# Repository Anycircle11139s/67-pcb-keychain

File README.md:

# 67-pcb-keychain
I made a custom 67 keychain that lights up when you connect it to your computer, phone or other device. I think it's really cool and I can't wait to take it to school once I build it.
<br>

<br>

<br>

<br>

<br>

BOM:
<br>

|Name              |Purpose                                |Quantity|Total Cost (USD)|Link                                                                                                                                                                                                                                                                                                                                                                                                                                                                                                                                                                                                                                                                                                                                                                               |Distributor|
|------------------|---------------------------------------|--------|----------------|-----------------------------------------------------------------------------------------------------------------------------------------------------------------------------------------------------------------------------------------------------------------------------------------------------------------------------------------------------------------------------------------------------------------------------------------------------------------------------------------------------------------------------------------------------------------------------------------------------------------------------------------------------------------------------------------------------------------------------------------------------------------------------------|-----------|
|tweezers          |to hold the small parts while soldering|1       |1.00            |https://www.aliexpress.com/item/1005008096741092.html?spm=a2g0o.productlist.main.5.7afbAQx3AQx30w&algo_pvid=4f139a33-dc3b-4da1-b521-8f96e63a979a&algo_exp_id=4f139a33-dc3b-4da1-b521-8f96e63a979a-4&pdp_ext_f=%7B%22order%22%3A%22131%22%2C%22eval%22%3A%221%22%2C%22fromPage%22%3A%22search%22%7D&pdp_npi=6%40dis%21USD%2110.81%210.99%21%21%2173.30%216.71%21%40210328df17767629735092456e2e81%2112000043710740481%21sea%21AU%217402515296%21X%211%210%21n_tag%3A-29911%3Bd%3Aef1e07f3%3Bm03_new_user%3A-29895%3BpisId%3A5000000204047332&curPageLogUid=6M5JIEKTcvOh&utparam-url=scene%3Asearch%7Cquery_from%3A%7Cx_object_id%3A1005008096741092%7C_p_origin_prod%3A                                                                                                             |ali express|
|soldering flux pen|to help me solder the smaller things   |1       |1.00            |https://www.aliexpress.com/item/1005005936689092.html?spm=a2g0o.productlist.main.7.4471xGxqxGxqcv&algo_pvid=2dcd025e-5ec3-4b9d-b2fd-4e3df81ab209&algo_exp_id=2dcd025e-5ec3-4b9d-b2fd-4e3df81ab209-6&pdp_ext_f=%7B%22order%22%3A%22353%22%2C%22spu_best_type%22%3A%22price%22%2C%22eval%22%3A%221%22%2C%22fromPage%22%3A%22search%22%7D&pdp_npi=6%40dis%21USD%216.21%210.99%21%21%2142.12%216.71%21%402101e2b017767628076321692e0a8b%2112000034926313078%21sea%21AU%217402515296%21X%211%210%21n_tag%3A-29911%3Bd%3Aef1e07f3%3Bm03_new_user%3A-29895%3BpisId%3A5000000204047332&curPageLogUid=JmLIlInXocJb&utparam-url=scene%3Asearch%7Cquery_from%3A%7Cx_object_id%3A1005005936689092%7C_p_origin_prod%3A                                                                          |ali express|
|5.1k resistor     |to resist                              |1       |0.72            |https://www.aliexpress.com/item/1005011924238866.html?spm=a2g0o.productlist.main.4.3264pH7SpH7SjC&aem_p4p_detail=202604210210197331387284447280000035590&algo_pvid=f58ab8a2-7106-4e3f-84a7-062609315ba7&algo_exp_id=f58ab8a2-7106-4e3f-84a7-062609315ba7-3&pdp_ext_f=%7B%22order%22%3A%22321%22%2C%22eval%22%3A%221%22%2C%22fromPage%22%3A%22search%22%7D&pdp_npi=6%40dis%21USD%210.53%210.53%21%21%210.53%210.53%21%40210311a017767626198982054e38ce%2112000057033019768%21sea%21AU%217402515296%21X%211%210%21n_tag%3A-29911%3Bd%3Aef1e07f3%3Bm03_new_user%3A-29895&curPageLogUid=cGjN7EKMtHuh&utparam-url=scene%3Asearch%7Cquery_from%3A%7Cx_object_id%3A1005011924238866%7C_p_origin_prod%3A&search_p4p_id=202604210210197331387284447280000035590_1                           |ali express|
|usb c receptacle  |so I can plug my computer in           |1       |1.99            |https://www.aliexpress.com/item/1005011803451264.html?productId=1005011803451264&pdp_ext_f=%7B%22eval%22:%221%22,%22fromPage%22:%22search%22,%22tabScene%22:%22retail%22,%22sku_id%22:12000056614035390,%22origProductId%22:%221005011803451264%22,%22order%22:%221%22%7D                                                                                                                                                                                                                                                                                                                                                                                                                                                                                                          |ali express|
|resetable fuse    |so no short circuit                    |1       |1.67            |https://www.aliexpress.com/item/1005008044907223.html?spm=a2g0o.productlist.main.1.4252CnoLCnoLpE&algo_pvid=10b5198a-0f95-4115-972e-984253eaf529&algo_exp_id=10b5198a-0f95-4115-972e-984253eaf529-0&pdp_ext_f=%7B%22order%22%3A%2279%22%2C%22spu_best_type%22%3A%22price%22%2C%22eval%22%3A%221%22%2C%22fromPage%22%3A%22search%22%7D&pdp_npi=6%40dis%21USD%211.67%211.67%21%21%2111.29%2111.29%21%402101d9ef17767616653342759ed8d3%2112000047100392319%21sea%21AU%217402515296%21X%211%210%21n_tag%3A-29911%3Bd%3Aef1e07f3%3Bm03_new_user%3A-29895&curPageLogUid=NiaW1SDH6kb0&utparam-url=scene%3Asearch%7Cquery_from%3A%7Cx_object_id%3A1005008044907223%7C_p_origin_prod%3A                                                                                                     |ali express|
|protection diode  |smth                                   |1       |3.37            |https://www.aliexpress.com/item/1005008923840036.html?spm=a2g0o.productlist.main.1.47e31EDi1EDimN&algo_pvid=5c20eac6-6718-47b1-babc-bcccb17ab28b&algo_exp_id=5c20eac6-6718-47b1-babc-bcccb17ab28b-0&pdp_ext_f=%7B%22order%22%3A%2227%22%2C%22eval%22%3A%221%22%2C%22fromPage%22%3A%22search%22%7D&pdp_npi=6%40dis%21USD%216.74%213.37%21%21%216.74%213.37%21%402103122117767612887433650ec1a9%2112000047220263093%21sea%21AU%217402515296%21X%211%210%21n_tag%3A-29911%3Bd%3Aef1e07f3%3Bm03_new_user%3A-29895&curPageLogUid=80s78qVBFCrP&utparam-url=scene%3Asearch%7Cquery_from%3A%7Cx_object_id%3A1005008923840036%7C_p_origin_prod%3A                                                                                                                                           |ali express|
|10uf capcitor kit |capacitate                             |1       |1.00            |https://www.aliexpress.com/item/1005010813164058.html?spm=a2g0o.productlist.main.4.7113wPJGwPJGCe&aem_p4p_detail=202604210142017673585286925940000030866&algo_pvid=14866327-1cc9-4166-a2fd-ecccc7aec23f&algo_exp_id=14866327-1cc9-4166-a2fd-ecccc7aec23f-3&pdp_ext_f=%7B%22order%22%3A%22184%22%2C%22eval%22%3A%221%22%2C%22fromPage%22%3A%22search%22%7D&pdp_npi=6%40dis%21USD%214.23%210.99%21%21%214.23%210.99%21%40210319b017767609214422619ea5ce%2112000055817174283%21sea%21AU%217402515296%21X%211%210%21n_tag%3A-29911%3Bd%3Aef1e07f3%3Bm03_new_user%3A-29895%3BpisId%3A5000000204047332&curPageLogUid=E53GmhCoiUTd&utparam-url=scene%3Asearch%7Cquery_from%3A%7Cx_object_id%3A1005010813164058%7C_p_origin_prod%3A&search_p4p_id=202604210142017673585286925940000030866_1|ali express|
|470r resistor     |to resist                              |1       |1.68            |https://www.aliexpress.com/item/1005006996501198.html?spm=a2g0o.productlist.main.1.1371Xnz8Xnz8kp&algo_pvid=fcb6f408-4475-4521-a71e-0347dbee9bc1&algo_exp_id=fcb6f408-4475-4521-a71e-0347dbee9bc1-0&pdp_ext_f=%7B%22order%22%3A%225183%22%2C%22eval%22%3A%221%22%2C%22orig_sl_item_id%22%3A%221005006996501198%22%2C%22orig_item_id%22%3A%221005009026349718%22%2C%22fromPage%22%3A%22search%22%7D&pdp_npi=6%40dis%21USD%213.07%211.54%21%21%2120.80%2110.40%21%40210318a717767607540031004ef39e%2112000038988519805%21sea%21AU%217402515296%21X%211%210%21n_tag%3A-29911%3Bd%3Aef1e07f3%3Bm03_new_user%3A-29895&curPageLogUid=iB6W90ivAqo3&utparam-url=scene%3Asearch%7Cquery_from%3A%7Cx_object_id%3A1005006996501198%7C_p_origin_prod%3A1005009026349718                        |Ali express|
|LEDs              |Lights                                 |1       |1.50            |https://www.aliexpress.com/item/1005012061605805.html?spm=a2g0o.productlist.main.2.730fdJHtdJHtLo&algo_pvid=7224a124-c8e1-4919-b808-c6958d6ca251&algo_exp_id=7224a124-c8e1-4919-b808-c6958d6ca251-1&pdp_ext_f=%7B%22order%22%3A%223%22%2C%22eval%22%3A%221%22%2C%22fromPage%22%3A%22search%22%7D&pdp_npi=6%40dis%21USD%212.83%211.42%21%21%2119.18%219.59%21%402101e07217767606246468606e65b4%2112000057410661971%21sea%21AU%217402515296%21X%211%210%21n_tag%3A-29911%3Bd%3Aef1e07f3%3Bm03_new_user%3A-29895&curPageLogUid=sk04RZeHjRZ9&utparam-url=scene%3Asearch%7Cquery_from%3A%7Cx_object_id%3A1005012061605805%7C_p_origin_prod%3A                                                                                                                                           |ali express|
|PCB               |The PCB                                |1       |5.50            |                                                                                                                                                                                                                                                                                                                                                                                                                                                                                                                                                                                                                                                                                                                                                                                   |JLCPCB     |

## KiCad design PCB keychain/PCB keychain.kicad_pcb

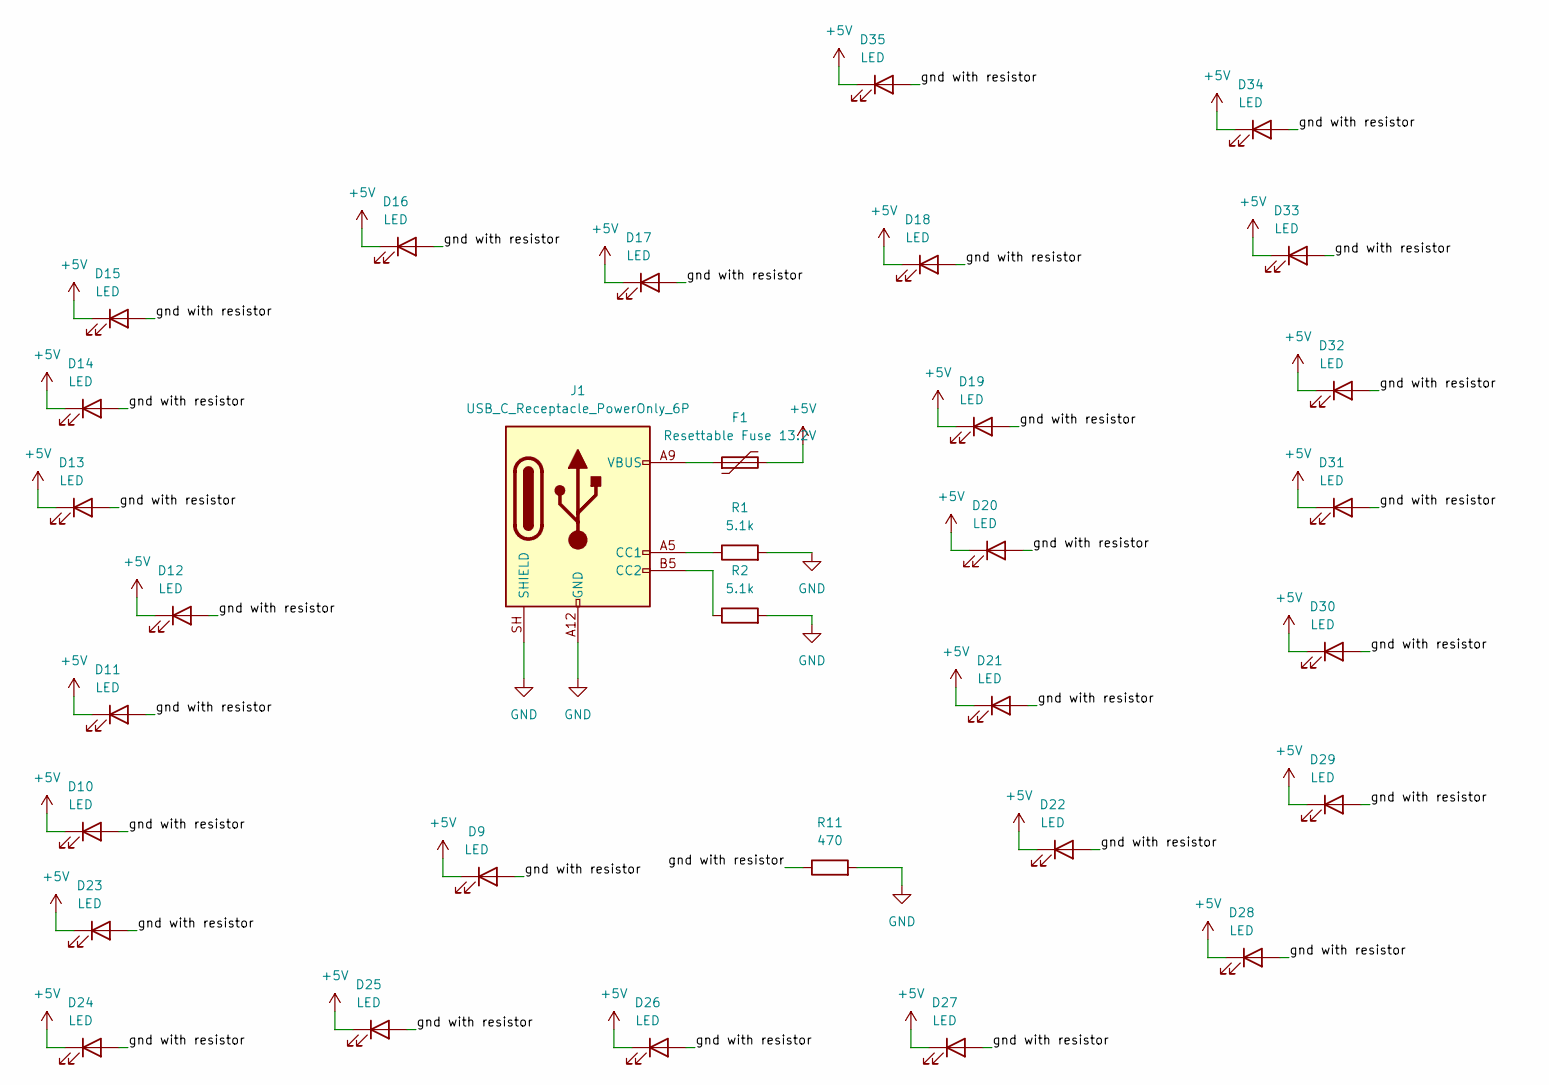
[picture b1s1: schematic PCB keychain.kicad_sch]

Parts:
D9, D10, D11, D12, D13, D14, D15, D16, D17, D18, D19, D20, D21, D22, D23, D24, D25, D26, D27, D28, D29, D30, D31, D32, D33, D34, D35: LED; LED_0805_2012Metric_Pad1.15x1.40mm_HandSolder
F1: Resettable Fuse 13.2V; Fuse_1206_3216Metric_Pad1.42x1.75mm_HandSolder
J1: USB_C_Receptacle_PowerOnly_6P; USB_C_Receptacle_GCT_USB4125-xx-x-0190_6P_TopMnt_Horizontal
R1, R2: 5.1k; R_0805_2012Metric_Pad1.20x1.40mm_HandSolder
R11: 470; R_0805_2012Metric_Pad1.20x1.40mm_HandSolder

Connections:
+5V: D9.1 (K), D10.1 (K), D11.1 (K), D12.1 (K), D13.1 (K), D14.1 (K), D15.1 (K), D16.1 (K), D17.1 (K), D18.1 (K), D19.1 (K), D20.1 (K), D21.1 (K), D22.1 (K), D23.1 (K), D24.1 (K), D25.1 (K), D26.1 (K), D27.1 (K), D28.1 (K), D29.1 (K), D30.1 (K), D31.1 (K), D32.1 (K), D33.1 (K), D34.1 (K), D35.1 (K), F1.2
/gnd with resistor: D9.2 (A), D10.2 (A), D11.2 (A), D12.2 (A), D13.2 (A), D14.2 (A), D15.2 (A), D16.2 (A), D17.2 (A), D18.2 (A), D19.2 (A), D20.2 (A), D21.2 (A), D22.2 (A), D23.2 (A), D24.2 (A), D25.2 (A), D26.2 (A), D27.2 (A), D28.2 (A), D29.2 (A), D30.2 (A), D31.2 (A), D32.2 (A), D33.2 (A), D34.2 (A), D35.2 (A), R11.1
GND: J1.A12 (GND), J1.B12 (GND), J1.SH (SHIELD), R1.2, R2.2, R11.2
unnamed: F1.1, J1.A9 (VBUS), J1.B9 (VBUS)
unnamed: J1.A5 (CC1), R1.1
unnamed: J1.B5 (CC2), R2.1

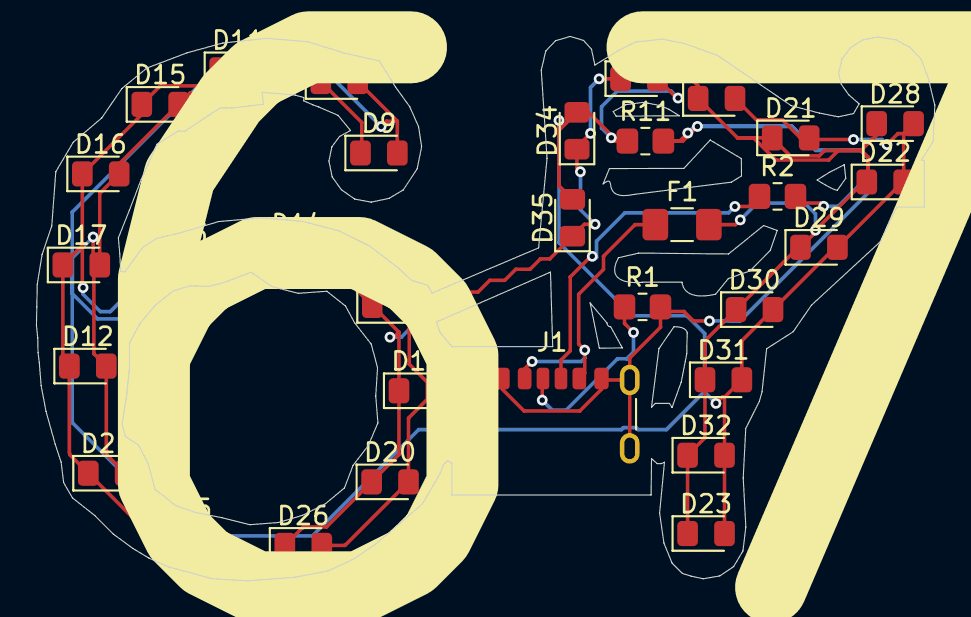
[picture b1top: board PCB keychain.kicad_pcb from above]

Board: 2 copper layers, 49.9 x 30.2 mm, 32 parts (0 on the bottom side), 6 nets.

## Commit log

2026-05-16 Rename PCB Keychain BOM.csv to BOM.csv
